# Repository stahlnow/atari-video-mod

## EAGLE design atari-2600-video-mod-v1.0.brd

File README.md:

# BOM

| Part                              | Value       | Device              | Package             | Description                                                                                                                                                                                                        |
|-----------------------------------|-------------|---------------------|---------------------|--------------------------------------------------------------------------------------------------------------------------------------------------------------------------------------------------------------------|
| C1, C7, C8, C9                    | 100nF       | CAP1206             | 1206                | Capacitor                                                                                                                                                                                                          |
| C2                                | 100uF       | CPOL-USD            | PANASONIC_D         | POLARIZED CAPACITOR, American symbol                                                                                                                                                                               |
| C3, C4                            | 10uF        | CPOL-USB            | PANASONIC_B         | POLARIZED CAPACITOR, American symbol                                                                                                                                                                               |
| C5                                | 50nF        | CAP1206             | 1206                | Capacitor                                                                                                                                                                                                          |
| C6                                | 250uF       | CPOL-USD            | PANASONIC_D         | POLARIZED CAPACITOR, American symbol                                                                                                                                                                               |
| C10                               | 10uF        | CAP1206             | 1206                | Capacitor                                                                                                                                                                                                          |
| D1                                | 1N914       | DIODE-SOD80C        | SOD80C              | DIODE                                                                                                                                                                                                              |
| IC1                               | LM386       | LM386M-1            | SO08                | Low Voltage Audio Power Amplifier                                                                                                                                                                                  |
| JP1                               |             | M03LONGPADS         | 1X03_LONGPADS       | Header 3                                                                                                                                                                                                           |
| Q1                                | 2N3904      | TRANSISTOR_NPNSOT23 | SOT23               | Generic NPN BJT                                                                                                                                                                                                    |
| R1                                | 1.8K        | RESISTOR1206        | 1206                | Resistor                                                                                                                                                                                                           |
| R2, R9                            | 10          | RESISTOR1206        | 1206                | Resistor                                                                                                                                                                                                           |
| R3                                | 1.5K        | RESISTOR1206        | 1206                | Resistor                                                                                                                                                                                                           |
| R4                                | 18K         | RESISTOR1206        | 1206                | Resistor                                                                                                                                                                                                           |
| R5                                | 9.1K        | RESISTOR1206        | 1206                | Resistor                                                                                                                                                                                                           |
| R6                                | 36K         | RESISTOR1206        | 1206                | Resistor                                                                                                                                                                                                           |
| R7                                | 1.6K        | RESISTOR1206        | 1206                | Resistor                                                                                                                                                                                                           |
| R8                                | 2K          | RESISTOR1206        | 1206                | Resistor                                                                                                                                                                                                           |
| R10, R12, R13, R14, R15, R16, R17 | 75          | RESISTOR1206        | 1206                | Resistor                                                                                                                                                                                                           |
| R11                               | 1K          | RESISTOR1206        | 1206                | Resistor                                                                                                                                                                                                           |
| U1                                | CD74HC4050M | CD74HC4050M         | SOIC127P600X175-16N | High-Speed CMOS Logic Hex Buffers, Inverting and Non-Inverting                                                                                                                                                     |
| U2                                | FMS6400     | FMS6400             | SOIC-8              | The FMS6400-1 is a dual Y/C 5 -order Butterworth low-                                                                                                                                                              |
| X1, X2                            | M04X2       | M04X2               | 2X4                 | .1" header, two rows of four.                                                                                                                                                                                      |
| LOGO1                             | OSHW-LOGOS  | OSHW-LOGOS          | OSHW-LOGO-S         | Open Source Hardware Logo This logo indicates the piece of hardware it is found on incorporates a OSHW license and/or adheres to the definition of open source hardware found here: http://freedomdefined.org/OSHW |

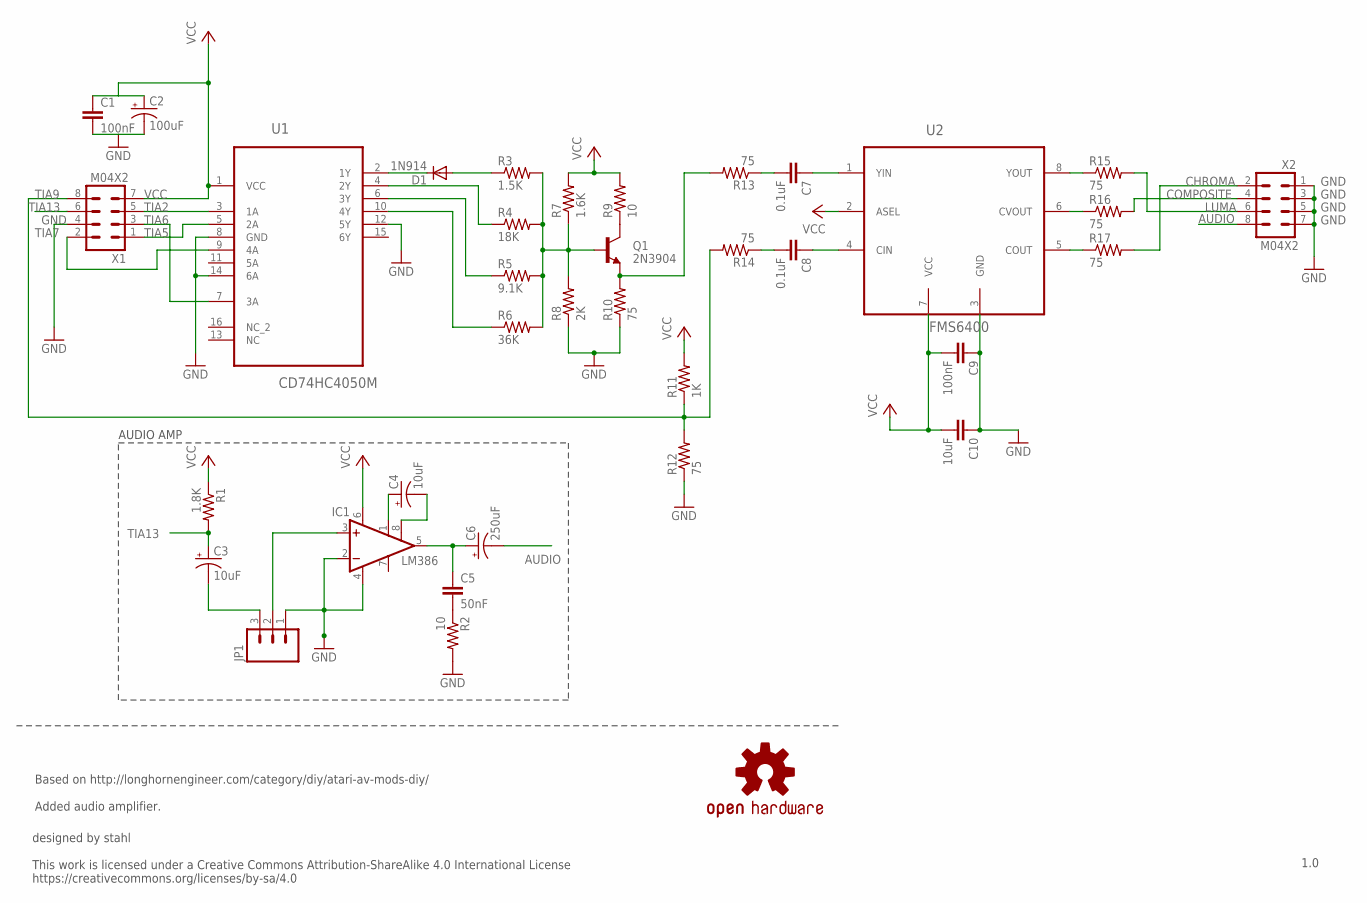
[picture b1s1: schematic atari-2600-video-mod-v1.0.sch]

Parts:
C1, C9: 100nF; 1206
C2: 100uF; PANASONIC_D
C3, C4: 10uF; PANASONIC_B
C5: 50nF; 1206
C6: 250uF; PANASONIC_D
C7, C8: 0.1uF; 1206
C10: 10uF; 1206
D1: 1N914; SOD80C
IC1: LM386; SO08
JP1: M03LONGPADS; 1X03_LONGPADS
LOGO1: OSHW-LOGOS; OSHW-LOGO-S
Q1: 2N3904; SOT23
R1: 1.8K; 1206
R2, R9: 10; 1206
R3: 1.5K; 1206
R4: 18K; 1206
R5: 9.1K; 1206
R6: 36K; 1206
R7: 1.6K; 1206
R8: 2K; 1206
R10, R12, R13, R14, R15, R16, R17: 75; 1206
R11: 1K; 1206
U1: CD74HC4050M; SOIC127P600X175-16N
U2: FMS6400; SOIC-8
X1, X2: M04X2; 2X4

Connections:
AUDIO: C6.-, X2.8
CHROMA: R17.2, X2.2
COMPOSITE: R16.2, X2.4
GND: C1.2, C2.-, C9.1, C10.1, IC1.2 (-IN), IC1.4 (GND), JP1.1, R2.2, R8.1, R10.1, R12.1, U1.8 (GND), U1.12 (5Y), U1.14 (6A), U2.3 (GND), X1.4, X2.1, X2.3, X2.5, X2.7
LUMA: R15.2, X2.6
unnamed: C8.1, U2.4 (CIN)
unnamed: R4.1, U1.4 (2Y)
unnamed: R5.1, U1.6 (3Y)
unnamed: R6.1, U1.10 (4Y)
unnamed: IC1.3 (+IN), JP1.2
unnamed: D1.C, U1.2 (1Y)
unnamed: D1.A, R3.1
unnamed: Q1.3 (C), R9.1
unnamed: Q1.2 (E), R10.2, R13.2
unnamed: C7.1, U2.1 (YIN)
unnamed: C7.2, R13.1
unnamed: C8.2, R14.1
unnamed: R15.1, U2.8 (YOUT)
unnamed: R17.1, U2.5 (COUT)
unnamed: R16.1, U2.6 (CVOUT)
unnamed: C4.+, IC1.1 (GAIN)
unnamed: C4.-, IC1.8 (GAIN)
unnamed: Q1.1 (B), R3.2, R4.2, R5.2, R6.2, R7.1, R8.2
unnamed: C5.2, R2.1
unnamed: C5.1, C6.+, IC1.5 (OUT)
unnamed: C3.-, JP1.3
TIA2: U1.3 (1A), X1.5
TIA5: U1.5 (2A), X1.1
TIA6: U1.7 (3A), X1.3
TIA7: U1.9 (4A), X1.2
TIA9: R11.1, R12.2, R14.2, X1.8
TIA13: C3.+, R1.2, X1.6
VCC: C1.1, C2.+, C9.2, C10.2, IC1.6 (VS), R1.1, R7.2, R9.2, R11.2, U1.1 (VCC), U2.2 (ASEL), U2.7 (VCC), X1.7

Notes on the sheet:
AUDIO AMP
Based on http://longhornengineer.com/category/diy/atari-av-mods-diy/ Added audio amplifier.
1.0

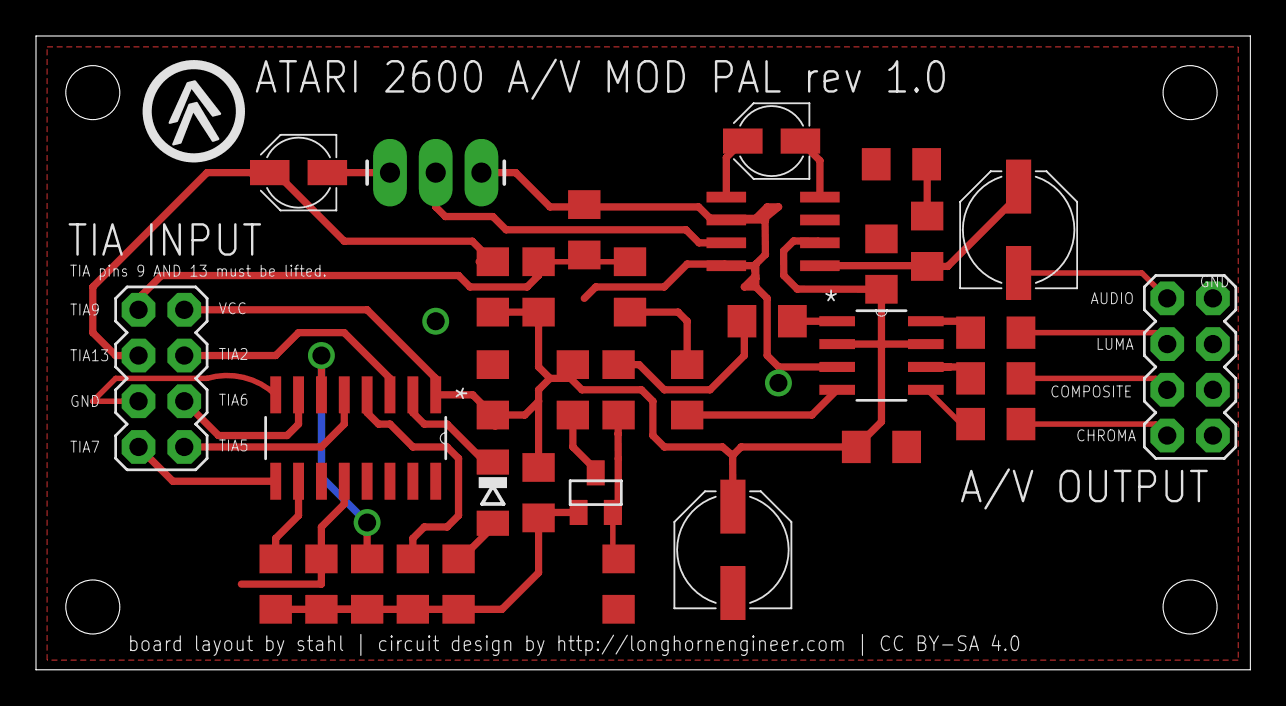
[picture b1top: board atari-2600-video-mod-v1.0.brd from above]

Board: 2 copper layers, 67.5 x 35.2 mm, 37 parts (1 on the bottom side), 33 nets.

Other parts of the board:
U$1: ATARI-AGE

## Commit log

2017-05-14 born
2017-05-14 :baby:
2017-05-14 ignore updated
2017-05-14 fixed logo :punch:
2017-05-16 add bom :punch:
2021-11-24 :art:

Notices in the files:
atari-2600-video-mod-v1.0.brd:
board layout by stahl | circuit design by http://longhornengineer.com | CC BY-SA 4.0
Released under the Creative Commons Attribution-ShareAlike 4.0 International License
https://creativecommons.org/licenses/by-sa/4.0
parts and their libraries:
SparkFun-Resistors: Licensing: CC v3.0 Share-Alike You are welcome to use this library for commercial purposes.
stahllabs: This work is licensed under a Creative Commons Attribution-ShareAlike 4.0 International License
stahllabs: Creative Commons License
